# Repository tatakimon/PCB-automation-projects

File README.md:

# PCB-automation-projects
Here I will share my way of AI based automating pcb desings and things that I create

Its not possible to draw schematic as we are used to but its possible to give datasheet and obtain netlist (like csv file), and use this netlist directly in PCB layout. In layout phases, although its possible to place the components and route them, its still not as perfect as professional layouters. Yet, its quite helpful to categorize similar components like LEDs, and place them in a neat way. 

Long story short, this project convert the traditional mouse click and draw technique to uploading datasheet, sharing what custom design is intended and have the completed netlist, together with schematic imaging.

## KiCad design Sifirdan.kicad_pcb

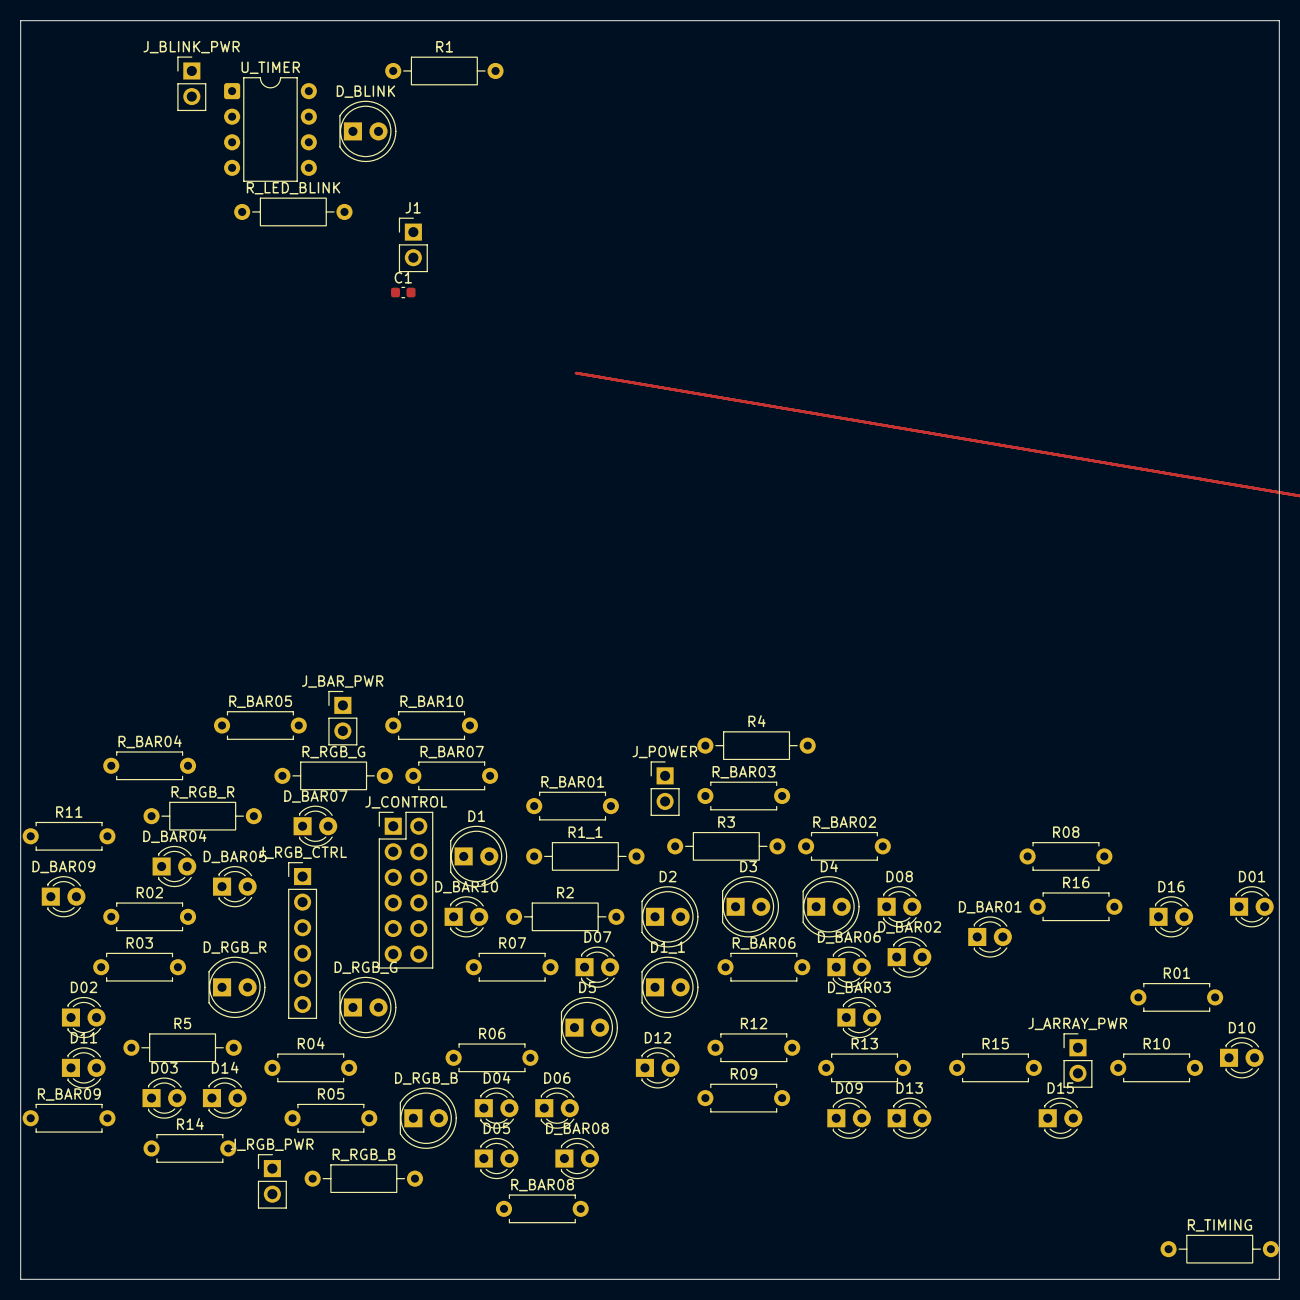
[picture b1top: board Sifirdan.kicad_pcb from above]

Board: 2 copper layers, 125.0 x 125.0 mm, 83 parts (0 on the bottom side), 62 nets.

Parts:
C1: 100nF; C_0603_1608Metric
D01, D02, D03, D04, D05, D06, D07, D08, D09, D10, D11, D12, D13, D14, D15, D16: Red; LED_D3.0mm
D1, D1_1: Red; LED_D5.0mm
D2: Green; LED_D5.0mm
D3: Blue; LED_D5.0mm
D4: Yellow; LED_D5.0mm
D5: White; LED_D5.0mm
D_BAR01, D_BAR02, D_BAR03, D_BAR04, D_BAR05, D_BAR06: Green; LED_D3.0mm
D_BAR07, D_BAR08: Yellow; LED_D3.0mm
D_BAR09, D_BAR10: Red; LED_D3.0mm
D_BLINK: Red; LED_D5.0mm
D_RGB_B: Blue; LED_D5.0mm
D_RGB_G: Green; LED_D5.0mm
D_RGB_R: Red; LED_D5.0mm
J1: Conn_01x02_Pin; PinHeader_1x02_P2.54mm_Vertical
J_ARRAY_PWR: Conn_01x02_Pin; PinHeader_1x02_P2.54mm_Vertical
J_BAR_PWR: Conn_01x02_Pin; PinHeader_1x02_P2.54mm_Vertical
J_BLINK_PWR: Conn_01x02_Pin; PinHeader_1x02_P2.54mm_Vertical
J_CONTROL: Conn_02x06_Odd_Even; PinHeader_2x06_P2.54mm_Vertical
J_POWER: Conn_01x02_Pin; PinHeader_1x02_P2.54mm_Vertical
J_RGB_CTRL: Conn_01x06_Pin; PinHeader_1x06_P2.54mm_Vertical
J_RGB_PWR: Conn_01x02_Pin; PinHeader_1x02_P2.54mm_Vertical
R01, R02, R03, R04, R05, R06, R07, R08, R09, R10, R11, R12, R13, R14, R15, R16: 470; R_Axial_DIN0207_L6.3mm_D2.5mm_P7.62mm_Horizontal
R1, R1_1, R2, R4: 330; R_Axial_DIN0207_L6.3mm_D2.5mm_P10.16mm_Horizontal
R3, R5: 220; R_Axial_DIN0207_L6.3mm_D2.5mm_P10.16mm_Horizontal
R_BAR01, R_BAR02, R_BAR03, R_BAR04, R_BAR05, R_BAR06, R_BAR07, R_BAR08, R_BAR09, R_BAR10: 470; R_Axial_DIN0207_L6.3mm_D2.5mm_P7.62mm_Horizontal
R_LED_BLINK: 330; R_Axial_DIN0207_L6.3mm_D2.5mm_P10.16mm_Horizontal
R_RGB_B: 220; R_Axial_DIN0207_L6.3mm_D2.5mm_P10.16mm_Horizontal
R_RGB_G: 330; R_Axial_DIN0207_L6.3mm_D2.5mm_P10.16mm_Horizontal
R_RGB_R: 330; R_Axial_DIN0207_L6.3mm_D2.5mm_P10.16mm_Horizontal
R_TIMING: 100k; R_Axial_DIN0207_L6.3mm_D2.5mm_P10.16mm_Horizontal
U_TIMER: NE555P; DIP-8_W7.62mm

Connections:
GND: C1.2, D1.2, J1.2
GND_1: D1_1.2, D2.2, D3.2, D4.2, D5.2, J_POWER.2
GND_2: D01.2, D02.2, D03.2, D04.2, D05.2, D06.2, D07.2, D08.2, D09.2, D10.2, D11.2, D12.2, D13.2, D14.2, D15.2, D16.2, J_ARRAY_PWR.2
GND_3: D_BAR01.2, D_BAR02.2, D_BAR03.2, D_BAR04.2, D_BAR05.2, D_BAR06.2, D_BAR07.2, D_BAR08.2, D_BAR09.2, D_BAR10.2, J_BAR_PWR.2, J_CONTROL.12
GND_4: D_RGB_B.2, D_RGB_G.2, D_RGB_R.2, J_RGB_CTRL.6, J_RGB_PWR.2
GND_5: D_BLINK.2, J_BLINK_PWR.2, U_TIMER.1
LED_CTRL_1: J_CONTROL.1, R_BAR01.1
LED_CTRL_2: J_CONTROL.2, R_BAR02.1
LED_CTRL_3: J_CONTROL.3, R_BAR03.1
LED_CTRL_4: J_CONTROL.4, R_BAR04.1
LED_CTRL_5: J_CONTROL.5, R_BAR05.1
LED_CTRL_6: J_CONTROL.6, R_BAR06.1
LED_CTRL_7: J_CONTROL.7, R_BAR07.1
LED_CTRL_8: J_CONTROL.8, R_BAR08.1
LED_CTRL_9: J_CONTROL.9, R_BAR09.1
LED_CTRL_10: J_CONTROL.10, R_BAR10.1
unnamed: D1.1, R1.2
unnamed: D1_1.1, R1_1.2
unnamed: D2.1, R2.2
unnamed: D3.1, R3.2
unnamed: D4.1, R4.2
unnamed: D5.1, R5.2
unnamed: D01.1, R01.2
unnamed: D02.1, R02.2
unnamed: D03.1, R03.2
unnamed: D04.1, R04.2
unnamed: D05.1, R05.2
unnamed: D06.1, R06.2
unnamed: D07.1, R07.2
unnamed: D08.1, R08.2
unnamed: D09.1, R09.2
unnamed: D10.1, R10.2
unnamed: D11.1, R11.2
unnamed: D12.1, R12.2
unnamed: D13.1, R13.2
unnamed: D14.1, R14.2
unnamed: D15.1, R15.2
unnamed: D16.1, R16.2
unnamed: D_BAR01.1, R_BAR01.2
unnamed: D_BAR02.1, R_BAR02.2
unnamed: D_BAR03.1, R_BAR03.2
unnamed: D_BAR04.1, R_BAR04.2
unnamed: D_BAR05.1, R_BAR05.2
unnamed: D_BAR06.1, R_BAR06.2
unnamed: D_BAR07.1, R_BAR07.2
unnamed: D_BAR08.1, R_BAR08.2
unnamed: D_BAR09.1, R_BAR09.2
unnamed: D_BAR10.1, R_BAR10.2
unnamed: D_RGB_R.1, R_RGB_R.2
unnamed: D_RGB_G.1, R_RGB_G.2
unnamed: D_RGB_B.1, R_RGB_B.2
unnamed: D_BLINK.1, R_LED_BLINK.2
RGB_BLUE_CTRL: J_RGB_CTRL.3, R_RGB_B.1
RGB_GREEN_CTRL: J_RGB_CTRL.2, R_RGB_G.1
RGB_RED_CTRL: J_RGB_CTRL.1, R_RGB_R.1
TIMER_OUTPUT: R_LED_BLINK.1, U_TIMER.3
VCC: J1.1, R1.1
VCC_1: J_POWER.1, R1_1.1, R2.1, R3.1, R4.1, R5.1
VCC_2: J_ARRAY_PWR.1, R01.1, R02.1, R03.1, R04.1, R05.1, R06.1, R07.1, R08.1, R09.1, R10.1, R11.1, R12.1, R13.1, R14.1, R15.1, R16.1
VCC_3: J_BAR_PWR.1, J_CONTROL.11
VCC_4: J_RGB_CTRL.5, J_RGB_PWR.1
VCC_5: J_BLINK_PWR.1, U_TIMER.8

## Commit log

2025-09-06 Add PCB project files
2025-11-21 .
    .
